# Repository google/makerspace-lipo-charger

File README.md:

This is in the early stages of prototyping a multi-port 1S Li-po charger.

Features include:

- Wide input voltage (approx 5-24V, untested)
- High charge current (up to ~2.5A, untested)
- Discharge circuit (to arbitrary voltage; connector is limiting factor --
  mosfet can do ~10A)
- (Upstream) microcontroller only involved in the slow loops ("is it charged
  yet?", not "is current limit hit?")
- Relatively inexpensive BOM (compared to all-in-one buck-based chargers)
- Relatively easy to solder (only one part smaller than SO-8 and 0603, no exposed pads)

Open questions:

- Do we need extra soft-start circuitry to avoid current spike at beginning of charge?
- Can we heatsink the discharge circuit so this stacks better (DPAK on back ground plane)?
- How small can we get this as a replaceable daughterboard?
- How will we mount it inside a case?
- Can we trust the sum of individual shunts for calculating used power budget?
- How will MCU stay alive while probing (or backing off)
- Is there a much better way to shut off discharge (second nmos is obvious, but expensive)

License: CC-BY 4.0 International

Disclaimer: This not an official Google product.

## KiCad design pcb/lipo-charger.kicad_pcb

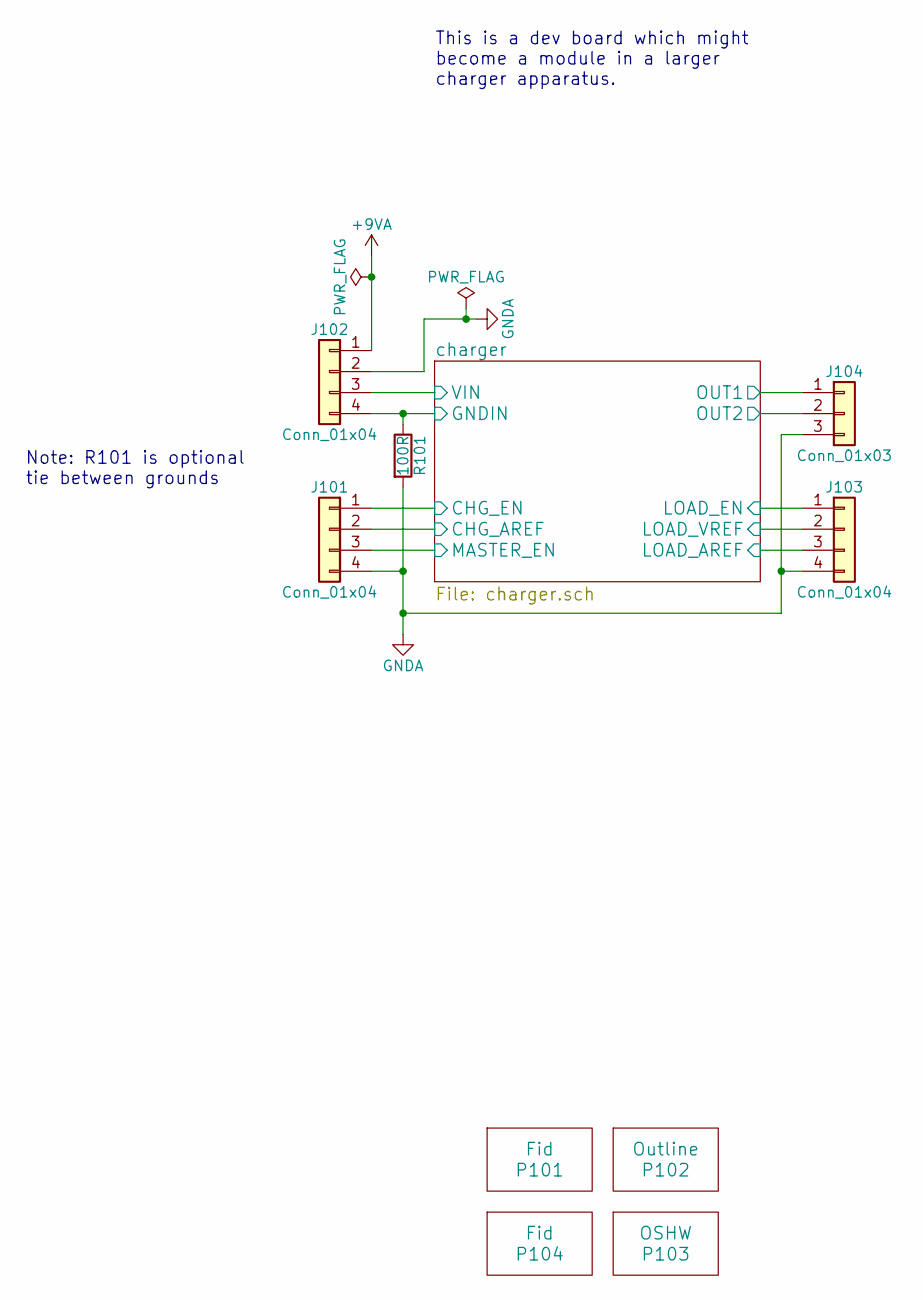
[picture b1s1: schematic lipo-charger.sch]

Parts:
J101, J102, J103: Conn_01x04; Molex_KK-6410-04_04x2.54mm_Straight
J104: Conn_01x03; Molex_KK-6410-03_03x2.54mm_Straight
P101, P104: Fid; Fiducial_1mm_Dia_2.54mm_Outer_CopperTop
P102: Outline; Board_Outline_48mm_Square
P103: OSHW; OSHW-Logo_7.5x8mm_SilkScreen
R101: 100R; R_0603_HandSoldering

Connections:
+9VA: J102.1; also elsewhere on the board
/charger/CHG_AREF: J101.2; also elsewhere on the board
/charger/CHG_EN: J101.1; also elsewhere on the board
/charger/GNDIN: J102.4, R101.1; also elsewhere on the board
/charger/LOAD_AREF: J103.3; also elsewhere on the board
/charger/LOAD_EN: J103.1; also elsewhere on the board
/charger/LOAD_VREF: J103.2; also elsewhere on the board
/charger/MASTER_EN: J101.3; also elsewhere on the board
/charger/OUT1: J104.1; also elsewhere on the board
/charger/OUT2: J104.2; also elsewhere on the board
/charger/VIN: J102.3; also elsewhere on the board
GNDA: J101.4, J102.2, J103.4, J104.3, R101.2; also elsewhere on the board

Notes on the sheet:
Note: R101 is optional tie between grounds
This is a dev board which might become a module in a larger charger apparatus.

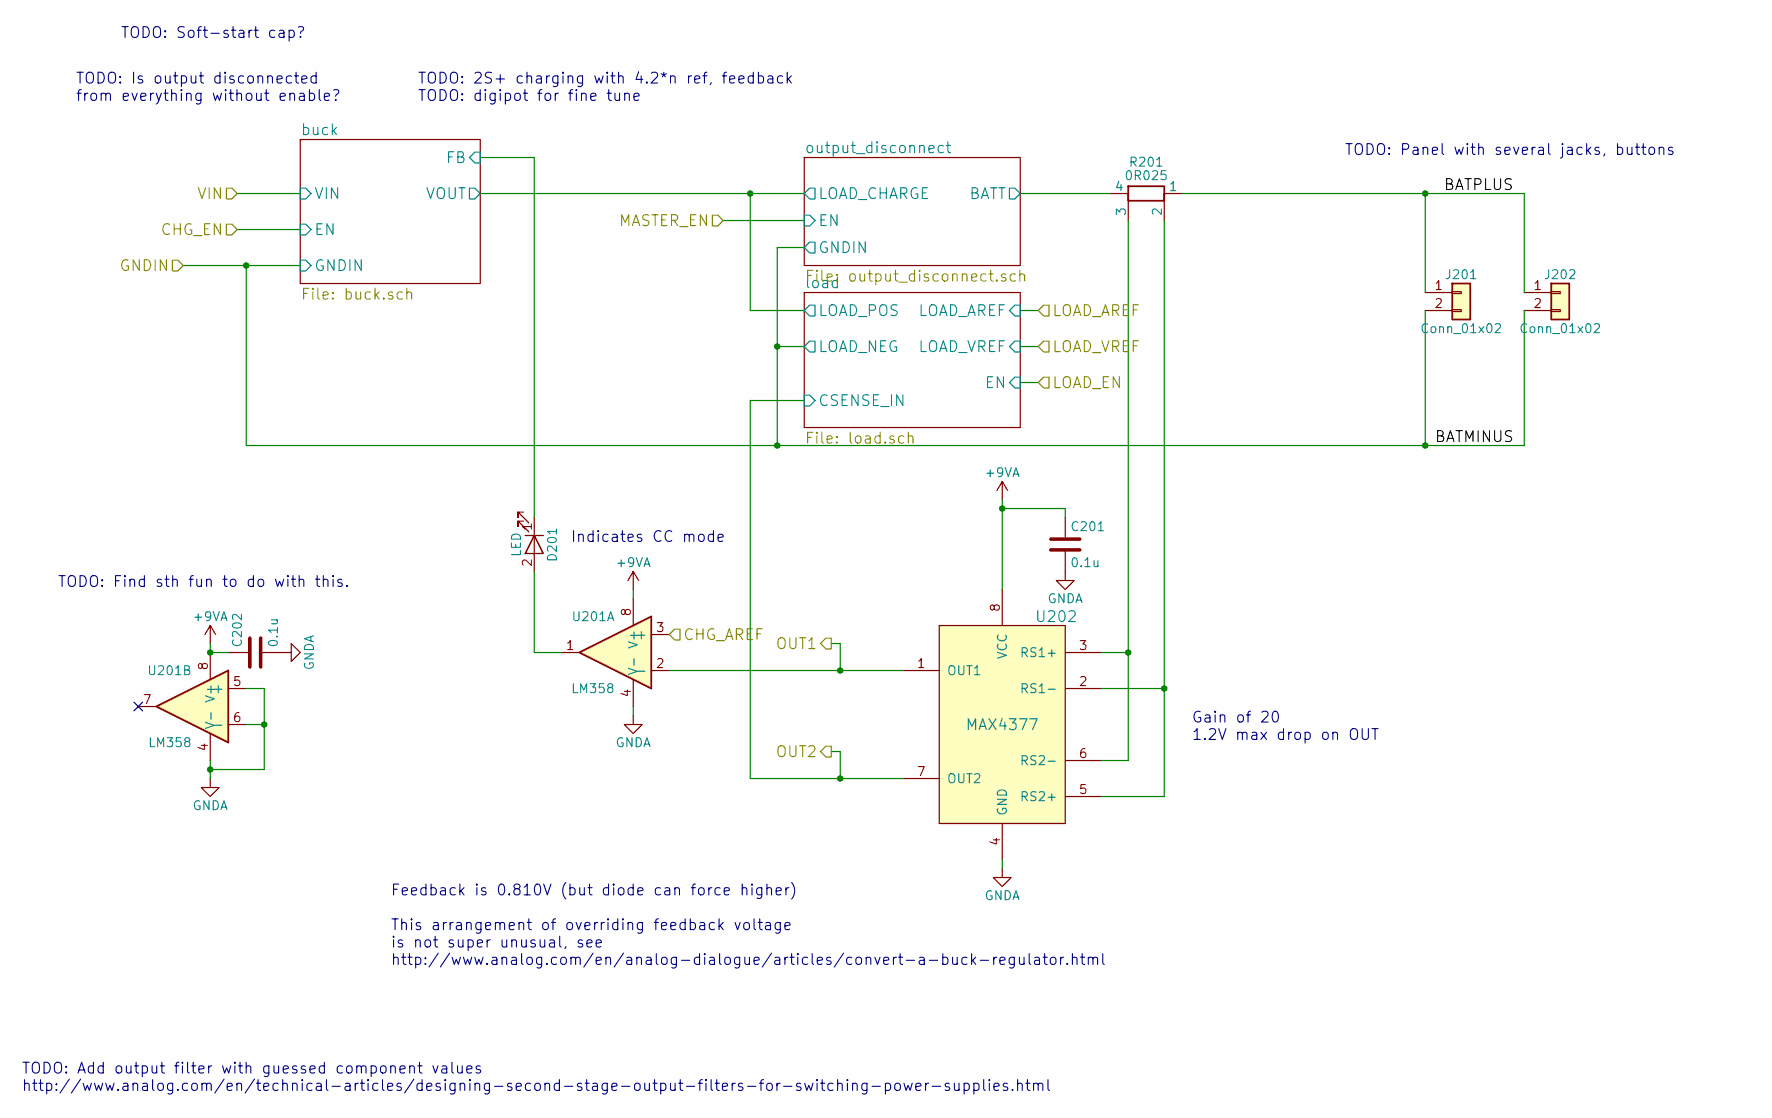
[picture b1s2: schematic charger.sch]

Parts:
C201, C202: 0.1u; C_0603
D201: LED; LED_0805_HandSoldering
J201: Conn_01x02; JST_PH_2_Combo
J202: Conn_01x02; JST_VH_B2PS-VH_2x2x3.96mm_Horizontal
R201: 0R025; R_2512_AD_Optimized
U201: LM358; SOIC-8_3.9x4.9mm_Pitch1.27mm
U202: MAX4377; SOIC-8_3.9x4.9mm_Pitch1.27mm; MPN MAX4377TASA+

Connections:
+9VA: C201.1, C202.1, U201.8 (V+), U202.8 (VCC); also elsewhere on the board
/charger/BATPLUS: J201.1, J202.1, R201.1
/charger/CHG_AREF: U201.3 (+); also elsewhere on the board
/charger/GNDIN: J201.2, J202.2; also elsewhere on the board
/charger/OUT1: U201.2 (-), U202.1 (OUT1); also elsewhere on the board
/charger/OUT2: U202.7 (OUT2); also elsewhere on the board
/charger/buck/FB: D201.1 (K); also elsewhere on the board
/charger/output_disconnect/BATT: R201.4; also elsewhere on the board
GNDA: C201.2, C202.2, U201.4 (V-), U201.5 (+), U201.6 (-), U202.4 (GND); also elsewhere on the board
unnamed: D201.2 (A), U201.1
unnamed: R201.2, U202.2 (RS1-), U202.5 (RS2+)
unnamed: R201.3, U202.3 (RS1+), U202.6 (RS2-)

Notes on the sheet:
Feedback is 0.810V (but diode can force higher) This arrangement of overriding feedback voltage is not super unusual, see http://www.analog.com/en/analog-dialogue/articles/convert-a-buck-regulator.html
TODO: Add output filter with guessed component values http://www.analog.com/en/technical-articles/designing-second-stage-output-filters-for-switching-power-supplies.html
TODO: Panel with several jacks, buttons
Indicates CC mode
TODO: Soft-start cap?
TODO: Is output disconnected from everything without enable?
Gain of 20 1.2V max drop on OUT
TODO: 2S+ charging with 4.2*n ref, feedback TODO: digipot for fine tune
TODO: Find sth fun to do with this.

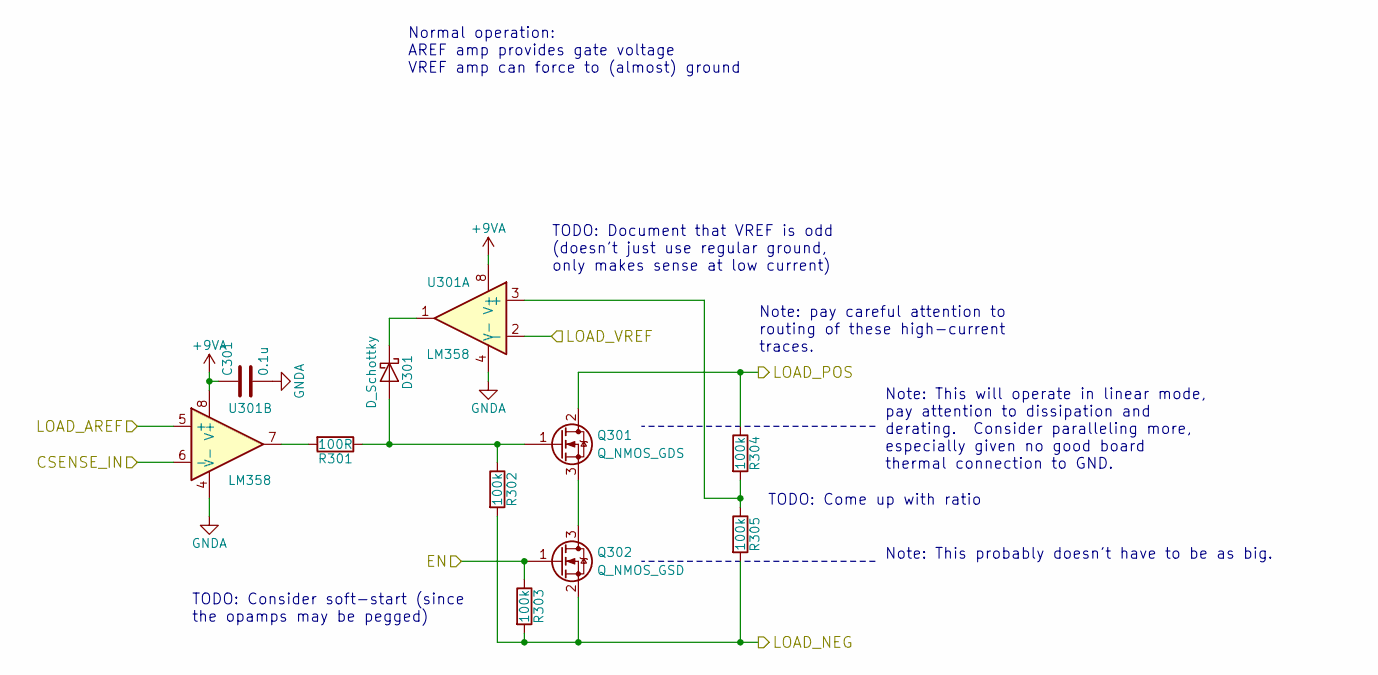
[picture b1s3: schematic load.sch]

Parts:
C301: 0.1u; C_0603
D301: D_Schottky; D_SOD-123
Q301: Q_NMOS_GDS; TO-252-2; MPN AO514
Q302: Q_NMOS_GSD; SOT-23_Handsoldering; MPN AO3400
R301: 100R; R_0603_HandSoldering
R302, R303, R304, R305: 100k; R_0603_HandSoldering
U301: LM358; SOIC-8_3.9x4.9mm_Pitch1.27mm

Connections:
+9VA: C301.1, U301.8 (V+); also elsewhere on the board
/charger/GNDIN: Q302.2 (S), R302.2, R303.2, R305.2; also elsewhere on the board
/charger/LOAD_AREF: U301.5 (+); also elsewhere on the board
/charger/LOAD_EN: Q302.1 (G), R303.1; also elsewhere on the board
/charger/LOAD_VREF: U301.2 (-); also elsewhere on the board
/charger/OUT2: U301.6 (-); also elsewhere on the board
/charger/output_disconnect/LOAD_CHARGE: Q301.2 (D), R304.1; also elsewhere on the board
GNDA: C301.2, U301.4 (V-); also elsewhere on the board
unnamed: D301.1 (K), U301.1
unnamed: D301.2 (A), Q301.1 (G), R301.1, R302.1
unnamed: Q301.3 (S), Q302.3 (D)
unnamed: R301.2, U301.7
unnamed: R304.2, R305.1, U301.3 (+)

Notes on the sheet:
Note: pay careful attention to routing of these high-current traces.
Normal operation: AREF amp provides gate voltage VREF amp can force to (almost) ground
Note: This will operate in linear mode, pay attention to dissipation and derating. Consider paralleling more, especially given no good board thermal connection to GND.
Note: This probably doesn't have to be as big.
TODO: Come up with ratio
TODO: Consider soft-start (since the opamps may be pegged)
TODO: Document that VREF is odd (doesn't just use regular ground, only makes sense at low current)

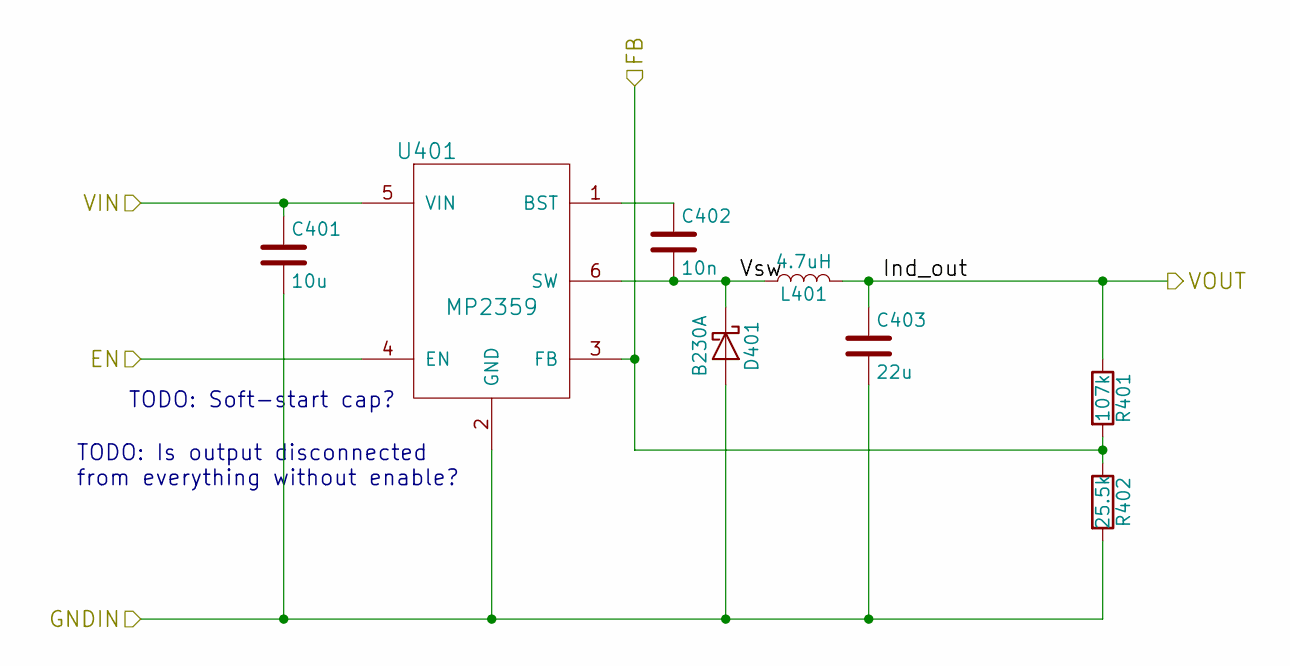
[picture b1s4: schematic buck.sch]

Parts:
C401: 10u; C_1206
C402: 10n; C_0603
C403: 22u; C_1206
D401: B230A; D_SMA
L401: 4.7uH; L_Taiyo-Yuden_NR-50xx
R401: 107k; R_0603_HandSoldering
R402: 25.5k; R_0603_HandSoldering
U401: MP2359; SOT-23-6_Handsoldering

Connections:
/charger/CHG_EN: U401.4 (EN); also elsewhere on the board
/charger/GNDIN: C401.2, C403.2, D401.2 (A), R402.2, U401.2 (GND); also elsewhere on the board
/charger/VIN: C401.1, U401.5 (VIN); also elsewhere on the board
/charger/buck/FB: R401.2, R402.1, U401.3 (FB); also elsewhere on the board
/charger/buck/Vsw: C402.2, D401.1 (K), L401.1, U401.6 (SW)
/charger/output_disconnect/LOAD_CHARGE: C403.1, L401.2, R401.1; also elsewhere on the board
unnamed: C402.1, U401.1 (BST)

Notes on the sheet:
TODO: Soft-start cap?
TODO: Is output disconnected from everything without enable?

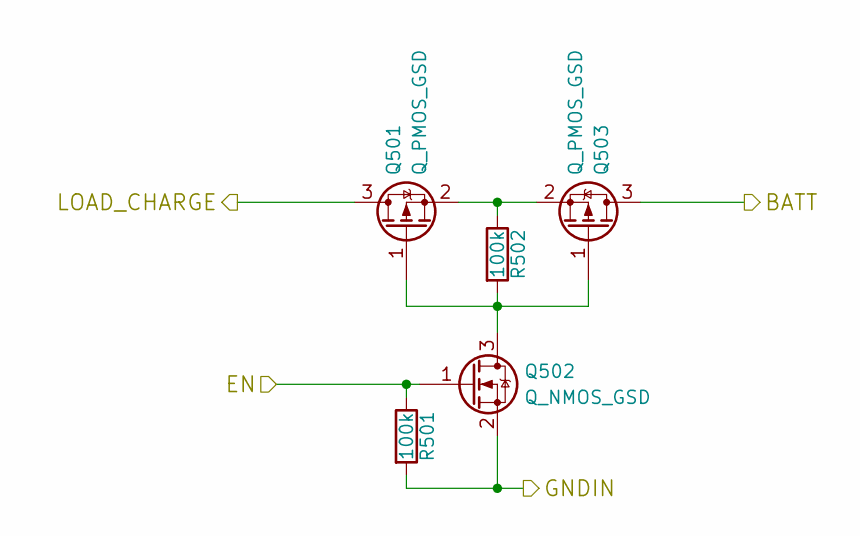
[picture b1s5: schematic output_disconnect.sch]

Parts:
Q501, Q503: Q_PMOS_GSD; SOT-23_Handsoldering
Q502: Q_NMOS_GSD; SOT-23_Handsoldering
R501, R502: 100k; R_0603_HandSoldering

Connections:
/charger/GNDIN: Q502.2 (S), R501.2; also elsewhere on the board
/charger/MASTER_EN: Q502.1 (G), R501.1; also elsewhere on the board
/charger/output_disconnect/BATT: Q503.3 (D); also elsewhere on the board
/charger/output_disconnect/LOAD_CHARGE: Q501.3 (D); also elsewhere on the board
unnamed: Q501.1 (G), Q502.3 (D), Q503.1 (G), R502.2
unnamed: Q501.2 (S), Q503.2 (S), R502.1

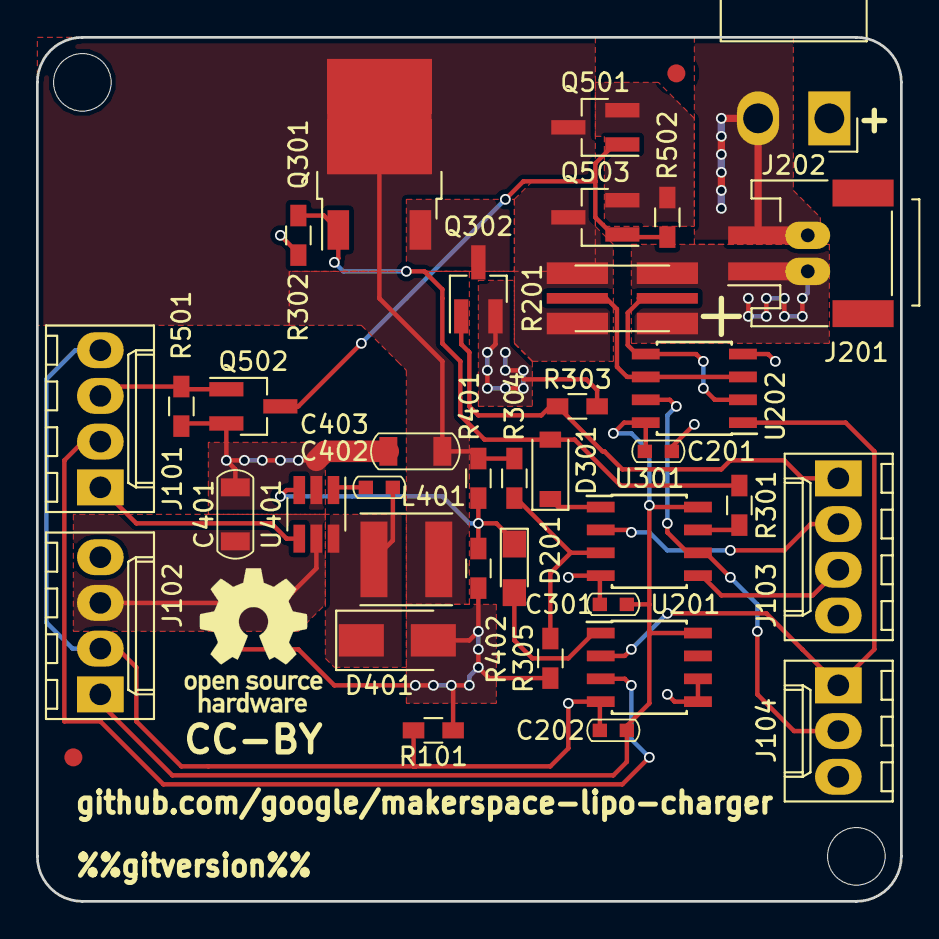
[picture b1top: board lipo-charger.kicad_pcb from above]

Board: 2 copper layers, 48.0 x 48.0 mm, 40 parts (0 on the bottom side), 28 nets.

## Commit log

2017-12-22 Add partsbin submodule
2017-12-22 Add gitignore and README
2017-12-22 Initial board, with relative paths
2017-12-22 Fix ERC/DRC errors for first prototype
2017-12-30 Massive rework, fully routed
2017-12-30 Add gitversion to pcb, minor tweaks
2018-01-18 Rename some nets, ordered.
2018-01-31 Add board render
2018-02-20 Fixup url and add license
2022-06-10 adding repo exemption for allstar security scanner
